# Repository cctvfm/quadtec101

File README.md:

# quadtec101
A Quad Panning Oscillator designed for the Neuztec 4 Festival

More info here: [cctv.fm](https://www.cctv.fm/product-page/quadtec-101)

Sign up here: [Neuzlab](http://www.neuztec.ca/neuzlab/)

>QUADTEC-101 A MUSICAL INSTRUMENT FROM THE FUTURE.

>THE GARDEN CITY ELECTRONIC MUSIC COMMUNITY CREATED A TIMEMACHINE USING RARE TELSA BLUEPRINTS AND WENT INTO THE FUTURE TO GATHER DATA OF THE DAY; SEEKING OUT INSTRUMENTS FROM THE CREATIVE YOUTH OF THE FUTURE. UPON RETURNING TO 2019 THEY BROUGHT THOSE IDEAS TO FILIP PIETRUSZEWSKI TO RE-ENGINEER, DESIGN, AND REALIZE THIS FUTURISTIC INSTRUMENT USING MODERN AND ANTIIQUE TOOLS AT HIS MAD SCIENCE LAB AT CAPITAL CITY TRANSISTOR AND VALVE.

# Licensing

CC BY-NC-SA

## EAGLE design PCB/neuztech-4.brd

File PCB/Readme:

This Folder Contains Eagle 9.12 SCH and BRD files, as well as gerbers ready to be sent out for manufacture.

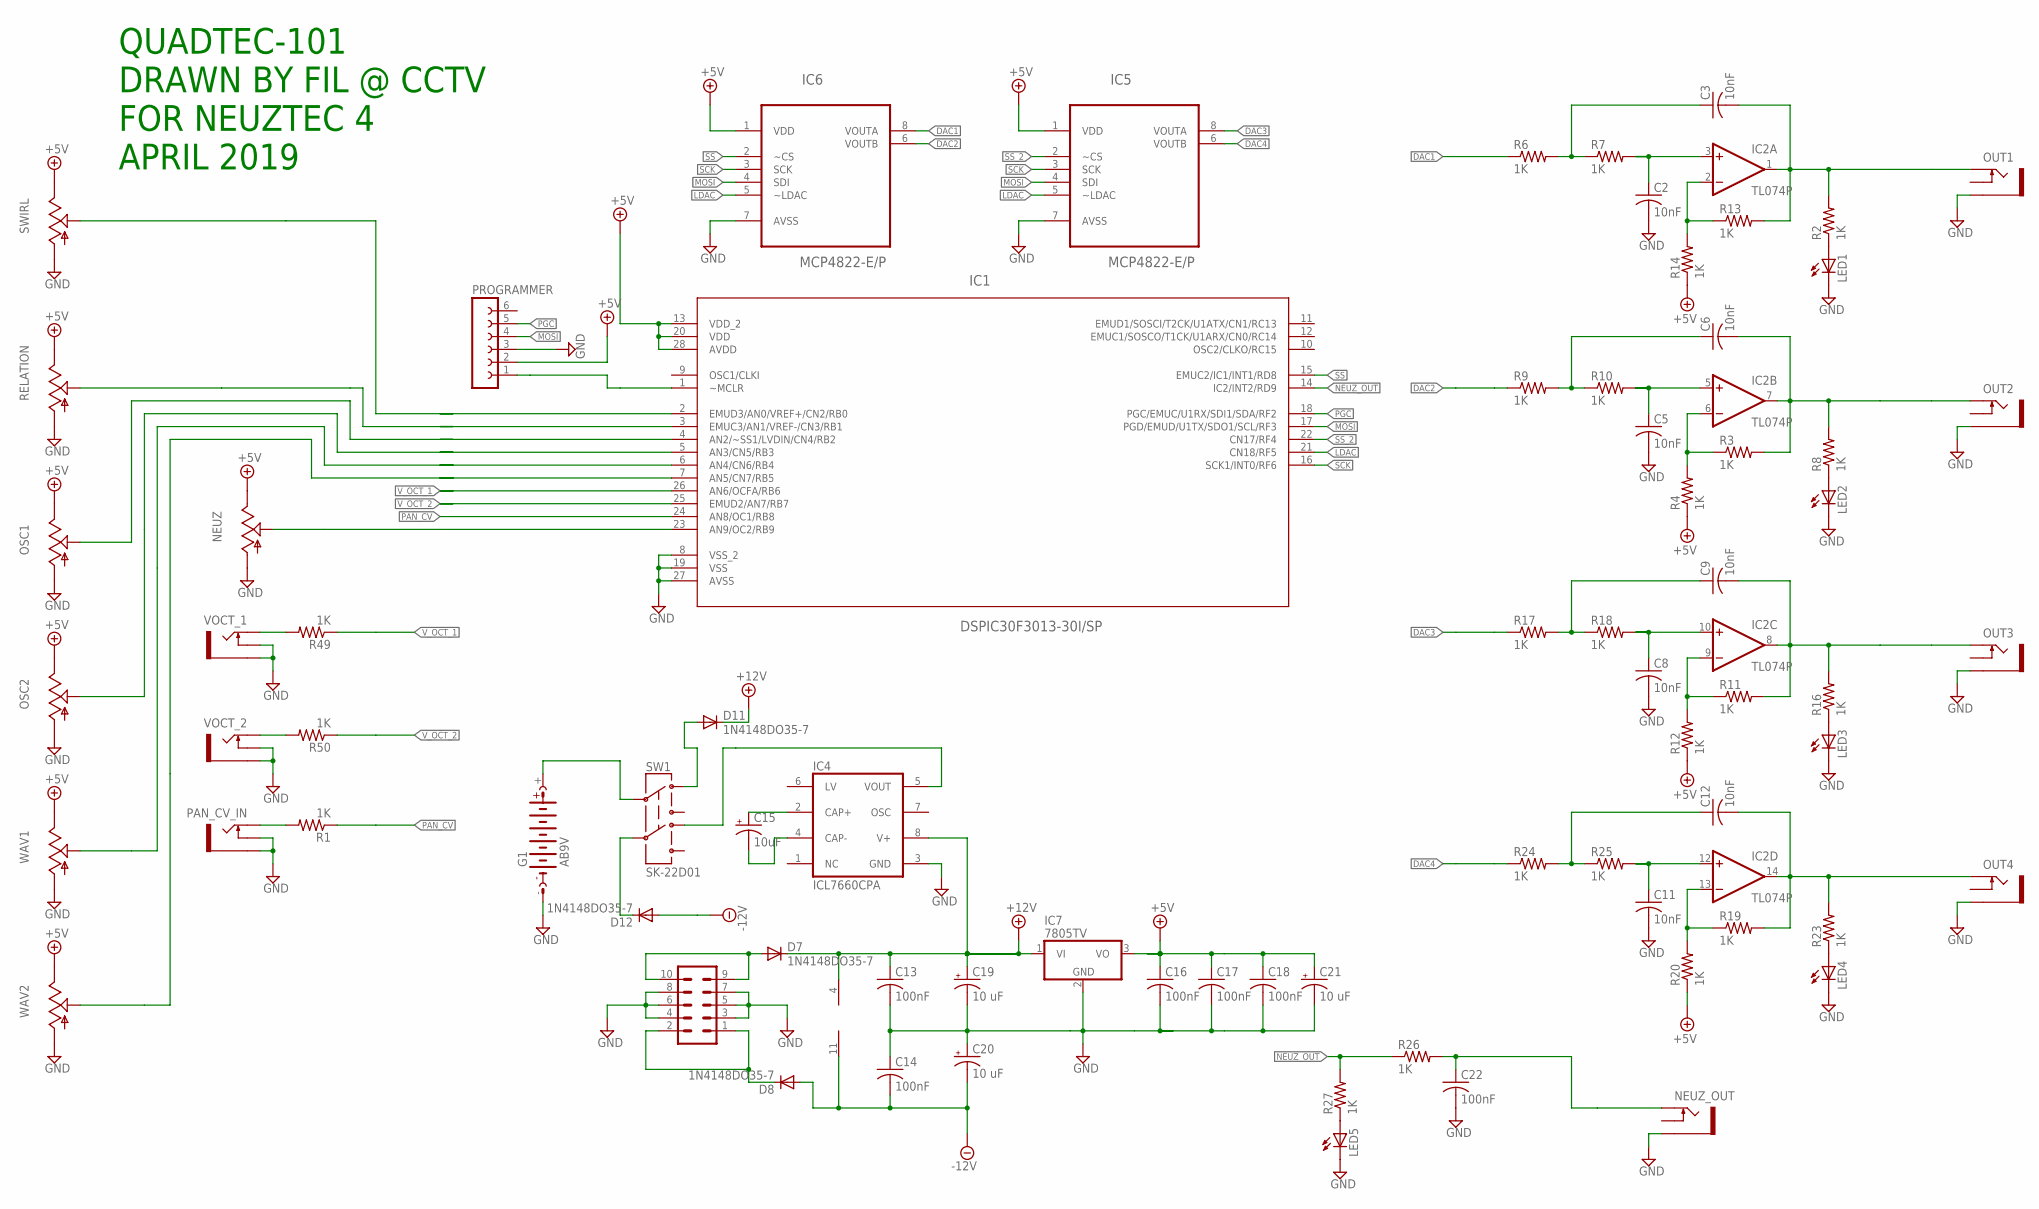
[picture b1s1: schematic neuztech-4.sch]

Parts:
C2, C3, C5, C6, C8, C9, C11, C12: 10nF; C050-035X075
C13, C14, C16, C17, C18, C22: 100nF; C050-024X044
C15: 10uF; E2-4
C19, C20, C21: 10 uF; E2-4
D7, D8, D11, D12: 1N4148DO35-7; DO35-7
G1: AB9V
IC1: DSPIC30F3013-30I/SP; DIP254P762X508-28
IC2: TL074P; DIL14
IC4: ICL7660CPA; DIL08
IC5, IC6: MCP4822-E/P; DIP254P762X432-8
IC7: 7805TV; TO220V
LED1, LED2, LED3, LED4, LED5: LED3MM
NEUZ: 9MM_SNAP-IN_POT_; 9MM_SNAP-IN_POT
NEUZ_OUT: THONKICONNNEW; WQP-PJ301M-12_JACK
OSC1, OSC2: 9MM_SNAP-IN_POT_; 9MM_SNAP-IN_POT
OUT1, OUT2, OUT3, OUT4: THONKICONNNEW; WQP-PJ301M-12_JACK
PAN_CV_IN: THONKICONNNEW; WQP-PJ301M-12_JACK
PROGRAMMER: FE06-1; FE06
R1, R2, R3, R4, R6, R7, R8, R9, R10, R11, R12, R13, R14, R16, R17, R18, R19, R20, R23, R24, R25, R26, R27, R49, R50: 1K; 0207/10
RELATION: 9MM_SNAP-IN_POT_; 9MM_SNAP-IN_POT
SV2: EURO_POWER_HEADERFAT_PADS; EURO_PWR_HEADER_FAT
SW1: SK-22D01; SK-22D01-MG
SWIRL: 9MM_SNAP-IN_POT_; 9MM_SNAP-IN_POT
VOCT_1, VOCT_2: THONKICONNNEW; WQP-PJ301M-12_JACK
WAV1, WAV2: 9MM_SNAP-IN_POT_; 9MM_SNAP-IN_POT

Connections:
+5V: C16.1, C17.1, C18.1, C21.+, IC1.13 (VDD_2), IC1.20 (VDD), IC1.28 (AVDD), IC5.1 (VDD), IC6.1 (VDD), IC7.3 (VO), NEUZ.3 (E), OSC1.3 (E), OSC2.3 (E), PROGRAMMER.2, R4.1, R12.1, R14.1, R20.1, RELATION.3 (E), SWIRL.3 (E), WAV1.3 (E), WAV2.3 (E)
+12V: C13.1, C19.+, D7.C, D11.C, IC2.4 (V+), IC4.8 (V+), IC7.1 (VI)
-12V: C14.2, C20.-, D8.A, D12.A, IC2.11 (V-)
DAC1: IC6.8 (VOUTA), R6.1
DAC2: IC6.6 (VOUTB), R9.1
DAC3: IC5.8 (VOUTA), R17.1
DAC4: IC5.6 (VOUTB), R24.1
GND: C2.2, C5.2, C8.2, C11.2, C13.2, C14.1, C16.2, C17.2, C18.2, C19.-, C20.+, C21.-, C22.2, G1.-, IC1.8 (VSS_2), IC1.19 (VSS), IC1.27 (AVSS), IC4.3 (GND), IC5.7 (AVSS), IC6.7 (AVSS), IC7.2 (GND), LED1.K (C), LED2.K (C), LED3.K (C), LED4.K (C), LED5.K (C), NEUZ.1 (A), NEUZ_OUT.P$3_SLEEVE (SLEEVE), OSC1.1 (A), OSC2.1 (A), OUT1.P$3_SLEEVE (SLEEVE), OUT2.P$3_SLEEVE (SLEEVE), OUT3.P$3_SLEEVE (SLEEVE), OUT4.P$3_SLEEVE (SLEEVE), PAN_CV_IN.P$2_SWITCH (SWITCH), PAN_CV_IN.P$3_SLEEVE (SLEEVE), PROGRAMMER.3, RELATION.1 (A), SV2.3, SV2.4, SV2.5, SV2.6, SV2.7, SV2.8, SWIRL.1 (A), VOCT_1.P$2_SWITCH (SWITCH), VOCT_1.P$3_SLEEVE (SLEEVE), VOCT_2.P$2_SWITCH (SWITCH), VOCT_2.P$3_SLEEVE (SLEEVE), WAV1.1 (A), WAV2.1 (A)
LDAC: IC1.21 (CN18/RF5), IC5.5 (~LDAC), IC6.5 (~LDAC)
MOSI: IC1.17 (PGD/EMUD/U1TX/SDO1/SCL/RF3), IC5.4 (SDI), IC6.4 (SDI), PROGRAMMER.4
unnamed: PAN_CV_IN.P$1_TIP (TIP), R1.2
unnamed: IC1.1 (~MCLR), PROGRAMMER.1
unnamed: C3.2, IC2.1 (OUT), OUT1.P$1_TIP (TIP), R2.2, R13.2
unnamed: LED1.A, R2.1
unnamed: C6.2, IC2.7 (OUT), OUT2.P$1_TIP (TIP), R3.2, R8.2
unnamed: IC2.6 (-IN), R3.1, R4.2
unnamed: C5.1, IC2.5 (+IN), R10.2
unnamed: C3.1, R6.2, R7.1
unnamed: LED2.A, R8.1
unnamed: C6.1, R9.2, R10.1
unnamed: D8.C, SV2.1, SV2.2
unnamed: C9.2, IC2.8 (OUT), OUT3.P$1_TIP (TIP), R11.2, R16.2
unnamed: IC2.9 (-IN), R11.1, R12.2
unnamed: C8.1, IC2.10 (+IN), R18.2
unnamed: LED3.A, R16.1
unnamed: IC2.2 (-IN), R13.1, R14.2
unnamed: C9.1, R17.2, R18.1
unnamed: D7.A, SV2.9, SV2.10
unnamed: C12.2, IC2.14 (OUT), OUT4.P$1_TIP (TIP), R19.2, R23.2
unnamed: IC2.13 (-IN), R19.1, R20.2
unnamed: C11.1, IC2.12 (+IN), R25.2
unnamed: C2.1, IC2.3 (+IN), R7.2
unnamed: LED4.A, R23.1
unnamed: C12.1, R24.2, R25.1
unnamed: LED5.A, R27.1
unnamed: C15.+, IC4.2 (CAP+)
unnamed: C22.1, NEUZ_OUT.P$1_TIP (TIP), R26.2
unnamed: C15.-, IC4.4 (CAP-)
unnamed: IC4.5 (VOUT), SW1.NC2
unnamed: G1.+, SW1.C1 (C)
unnamed: D11.A, SW1.NC1 (NC)
unnamed: D12.C, SW1.C2
unnamed: IC1.3 (EMUC3/AN1/VREF-/CN3/RB1), RELATION.2 (S)
unnamed: IC1.4 (AN2/~SS1/LVDIN/CN4/RB2), OSC1.2 (S)
unnamed: IC1.5 (AN3/CN5/RB3), OSC2.2 (S)
unnamed: IC1.6 (AN4/CN6/RB4), WAV1.2 (S)
unnamed: IC1.7 (AN5/CN7/RB5), WAV2.2 (S)
unnamed: IC1.2 (EMUD3/AN0/VREF+/CN2/RB0), SWIRL.2 (S)
unnamed: R50.2, VOCT_2.P$1_TIP (TIP)
unnamed: R49.2, VOCT_1.P$1_TIP (TIP)
NEUZ_OUT: IC1.14 (IC2/INT2/RD9), R26.1, R27.2
NEUZ_POT: IC1.23 (AN9/OC2/RB9), NEUZ.2 (S)
PAN_CV: IC1.24 (AN8/OC1/RB8), R1.1
PGC: IC1.18 (PGC/EMUC/U1RX/SDI1/SDA/RF2), PROGRAMMER.5
SCK: IC1.16 (SCK1/INT0/RF6), IC5.3 (SCK), IC6.3 (SCK)
SS: IC1.15 (EMUC2/IC1/INT1/RD8), IC6.2 (~CS)
SS_2: IC1.22 (CN17/RF4), IC5.2 (~CS)
V_OCT_1: IC1.26 (AN6/OCFA/RB6), R49.1
V_OCT_2: IC1.25 (EMUD2/AN7/RB7), R50.1

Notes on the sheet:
QUADTEC-101 DRAWN BY FIL @ CCTV FOR NEUZTEC 4 APRIL 2019

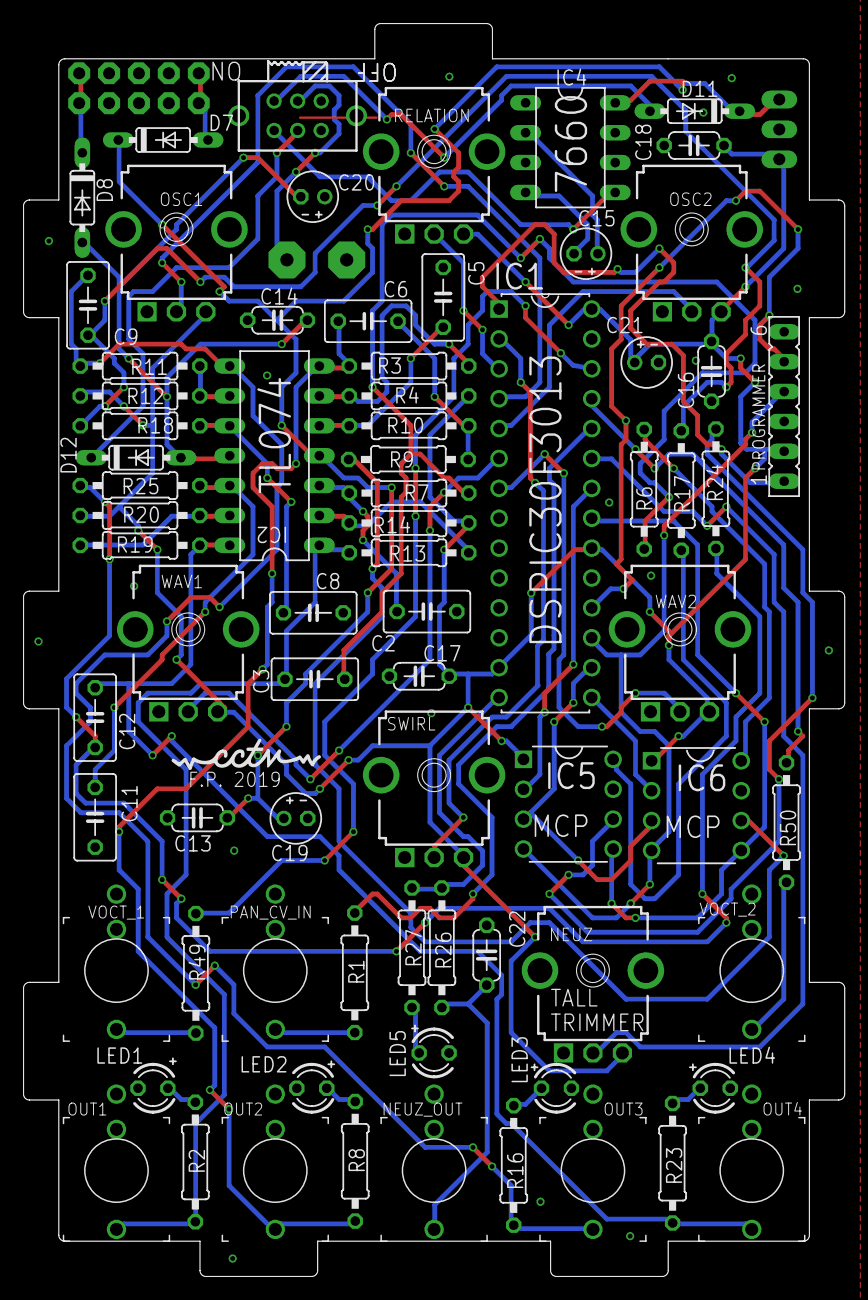
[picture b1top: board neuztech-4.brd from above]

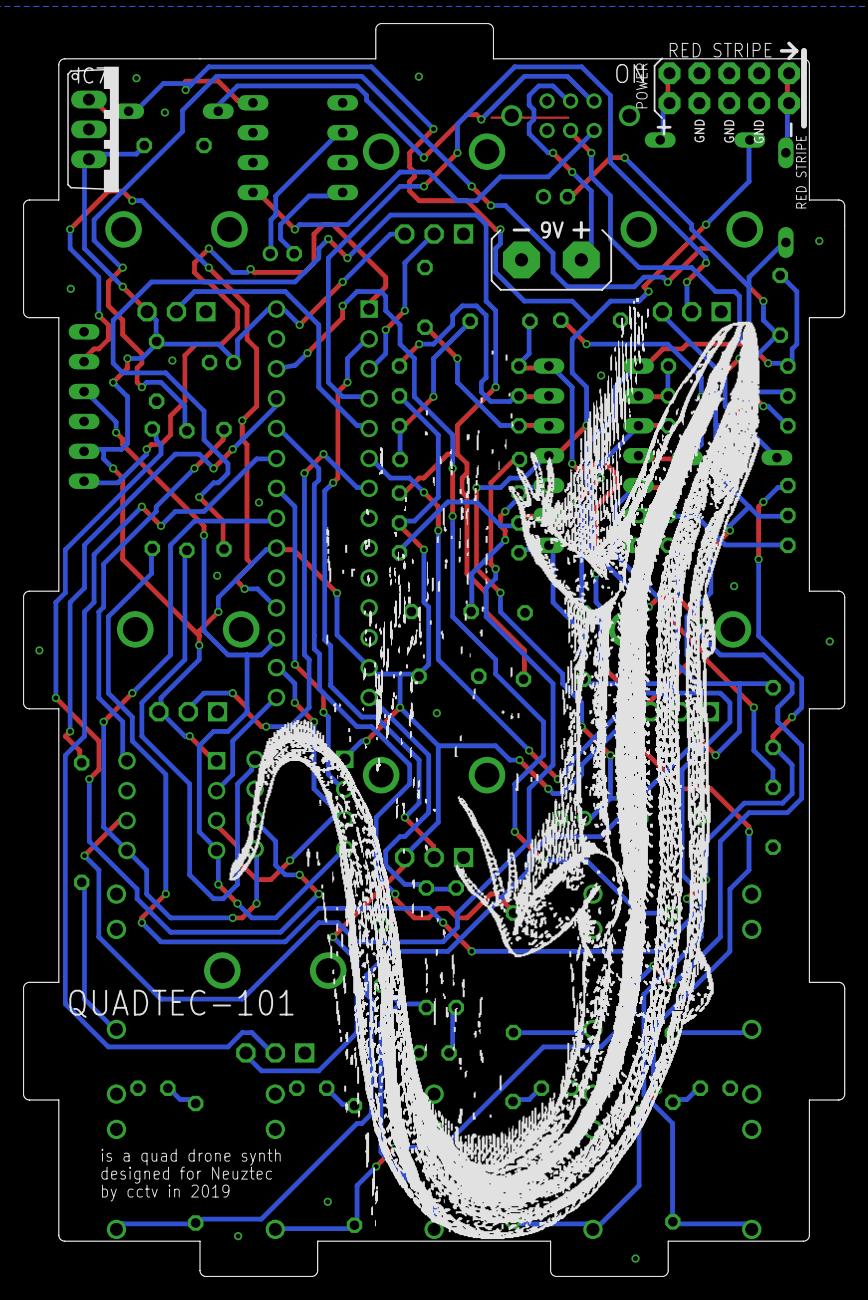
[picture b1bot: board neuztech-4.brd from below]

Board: 2 copper layers, 69.8 x 106.5 mm, 77 parts (4 on the bottom side), 59 nets.

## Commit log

2019-04-16 Uploaded schematics, gerbers, and BOM
2019-04-16 Uploaded images
2019-04-20 Uploaded finished Build Guide
2019-04-21 Create Mods
2019-04-22 Rearranged PCB Files
2019-05-13 New Build Guide V1.1
